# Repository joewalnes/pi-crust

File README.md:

Pi Crust
========

This is a PCB that brings sanity to Raspberry Pi headers.

See [http://picru.st](http://picru.st) for more.

Features
--------

*   Really compact - sits *inside* the surface area of the Raspberry Pi and adds less than 2mm to the height. If you have a case for your Raspberry Pi, this board should fit inside it.
*   Pins are grouped together: GPIO, I2C, SPI, UART and power.
*   Every pin is clearly labelled.
*   Connections: 2 x SPI, 2 x I2C, 1 x UART, 8 x GPIO
*   Uses female headers instead of male headers - you can poke jumpers right in.
*   Lots of GND and 5V pins - you need those guys a lot. These pins are duplicated where it makes sense (e.g. within the UART, I2C and SPI groups).
*   All thru-hole components - you can solder it yourself.
*   Cheapety cheapy cheap.
*   Open source hardware.
*   [More photos here](http://todayimade.co/items/joe-walnes-made-a-tiny-breakout-board-for-raspberry-pi)

See [http://picru.st](http://picru.st) for more.

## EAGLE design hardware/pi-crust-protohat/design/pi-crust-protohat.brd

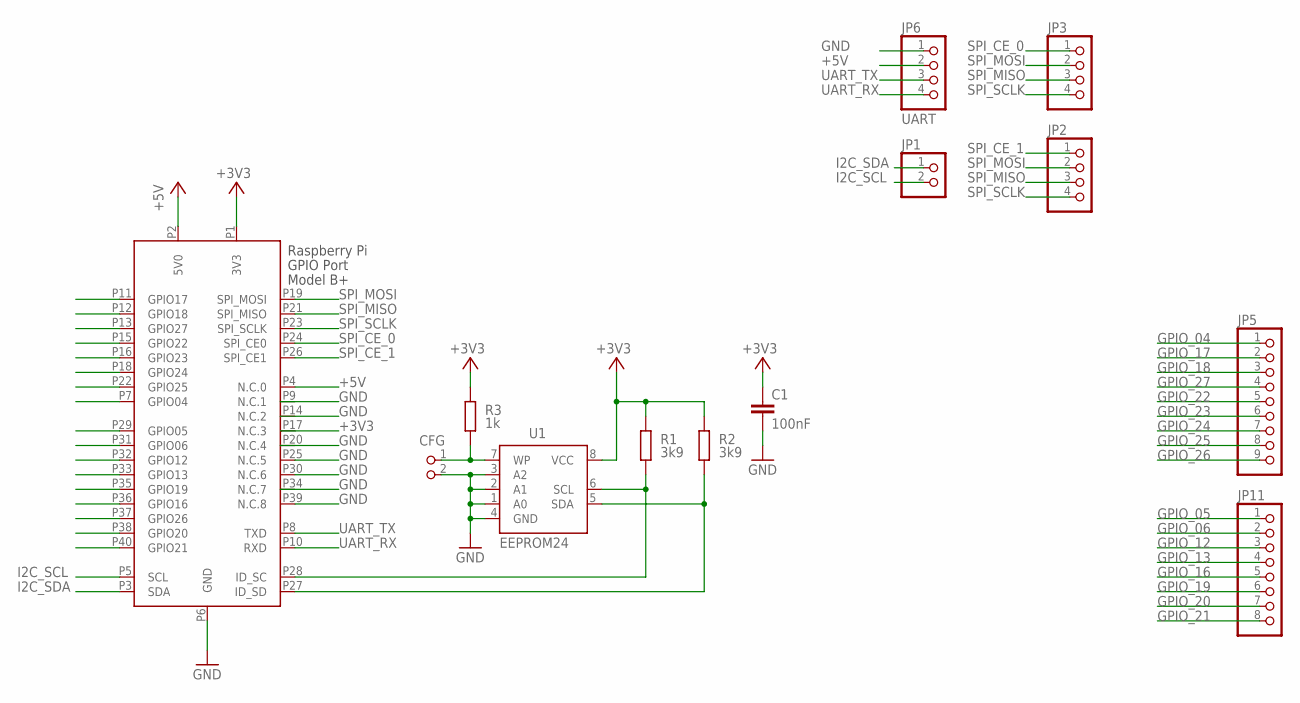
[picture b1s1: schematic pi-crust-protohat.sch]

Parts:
C1: 100nF; C0805K
CFG: PIN2_100; PIN_W_2
JP1: PINHD-1X2; 1X02
JP2, JP3: PINHD-1X4; 1X04
JP5: PINHD-1X9; 1X09
JP6: UART; 1X04
JP11: PINHD-1X8; 1X08
R1, R2: 3k9; M0805; TOLERANCE 5%
R3: 1k; M0805; TOLERANCE 5%
U1: EEPROM24; SOIC8
U$1: RASPI_BOARD_B+_SMD; RASPI_BOARD_B+_SMD_CONNECTOR

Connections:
+3V3: C1.1, R1.2, R2.2, R3.2, U1.8 (VCC), U$1.P1 (3V3)
+5V: JP6.2, U$1.P2 (5V0), U$1.P4 (N.C.0)
GND: C1.2, CFG.2, JP6.1, U1.1 (A0), U1.2 (A1), U1.3 (A2), U1.4 (GND), U$1.P6 (GND), U$1.P25 (N.C.5), U$1.P30 (N.C.6), U$1.P39 (N.C.8)
GPIO_04: JP5.1, U$1.P7 (GPIO04)
GPIO_05: JP11.1, U$1.P29 (GPIO05)
GPIO_06: JP11.2, U$1.P31 (GPIO06)
GPIO_12: JP11.3, U$1.P32 (GPIO12)
GPIO_13: JP11.4, U$1.P33 (GPIO13)
GPIO_16: JP11.5, U$1.P36 (GPIO16)
GPIO_17: JP5.2, U$1.P11 (GPIO17)
GPIO_18: JP5.3, U$1.P12 (GPIO18)
GPIO_19: JP11.6, U$1.P35 (GPIO19)
GPIO_20: JP11.7, U$1.P38 (GPIO20)
GPIO_21: JP11.8, U$1.P40 (GPIO21)
GPIO_22: JP5.5, U$1.P15 (GPIO22)
GPIO_23: JP5.6, U$1.P16 (GPIO23)
GPIO_24: JP5.7, U$1.P18 (GPIO24)
GPIO_25: JP5.8, U$1.P22 (GPIO25)
GPIO_26: JP5.9, U$1.P37 (GPIO26)
GPIO_27: JP5.4, U$1.P13 (GPIO27)
I2C_SCL: JP1.2, U$1.P5 (SCL)
I2C_SDA: JP1.1, U$1.P3 (SDA)
unnamed: CFG.1, R3.1, U1.7 (WP)
unnamed: R1.1, U1.6 (SCL), U$1.P28 (ID_SC)
unnamed: R2.1, U1.5 (SDA), U$1.P27 (ID_SD)
SPI_CE_0: JP3.1, U$1.P24 (SPI_CE0)
SPI_CE_1: JP2.1, U$1.P26 (SPI_CE1)
SPI_MISO: JP2.3, JP3.3, U$1.P21 (SPI_MISO)
SPI_MOSI: JP2.2, JP3.2, U$1.P19 (SPI_MOSI)
SPI_SCLK: JP2.4, JP3.4, U$1.P23 (SPI_SCLK)
UART_RX: JP6.4, U$1.P10 (RXD)
UART_TX: JP6.3, U$1.P8 (TXD)

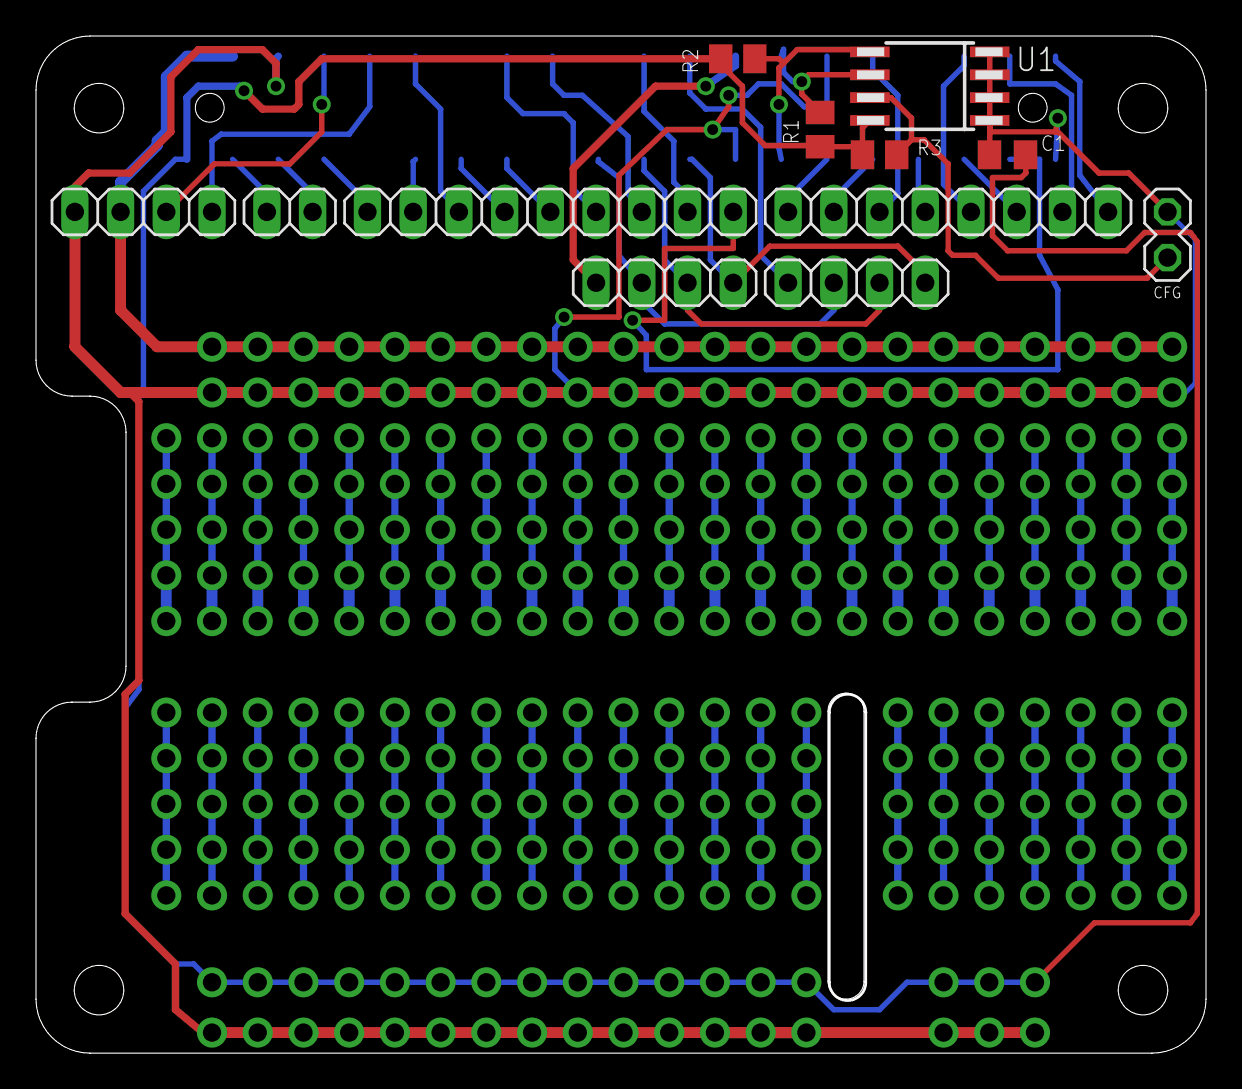
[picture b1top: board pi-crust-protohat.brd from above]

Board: 2 copper layers, 64.8 x 56.4 mm, 13 parts (0 on the bottom side), 32 nets.

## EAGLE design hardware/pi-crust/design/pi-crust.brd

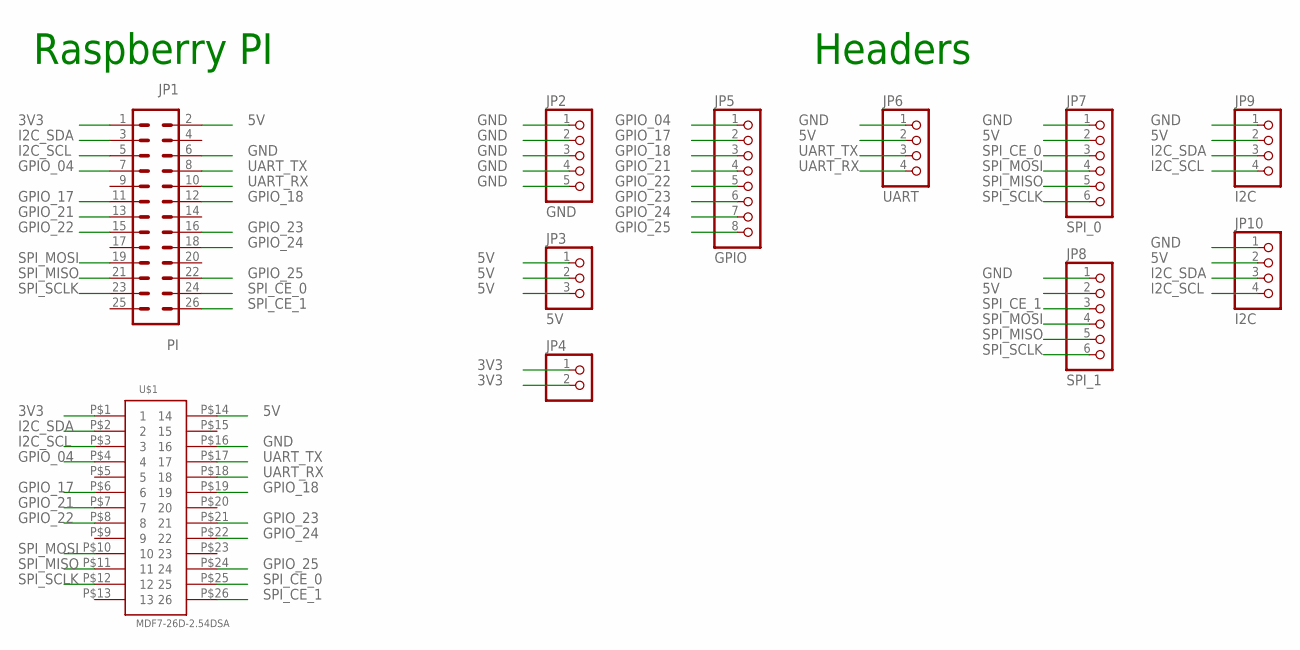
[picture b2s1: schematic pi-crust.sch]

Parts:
JP1: PI; MA13-2
JP2: GND; 1X05
JP3: 5V; 1X03
JP4: PINHD-1X2; 1X02
JP5: GPIO; 1X08
JP6: UART; 1X04
JP7: SPI_0; 1X06
JP8: SPI_1; 1X06
JP9, JP10: I2C; 1X04
U$1: MDF7-26D-2.54DSA

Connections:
3V3: JP1.1, JP4.1, JP4.2, U$1.P$1 (1)
5V: JP1.2, JP3.1, JP3.2, JP3.3, JP6.2, JP7.2, JP8.2, JP9.2, JP10.2, U$1.P$14 (14)
GND: JP1.6, JP2.1, JP2.2, JP2.3, JP2.4, JP2.5, JP6.1, JP7.1, JP8.1, JP9.1, JP10.1, U$1.P$16 (16)
GPIO_04: JP1.7, JP5.1, U$1.P$4 (4)
GPIO_17: JP1.11, JP5.2, U$1.P$6 (6)
GPIO_18: JP1.12, JP5.3, U$1.P$19 (19)
GPIO_21: JP1.13, JP5.4, U$1.P$7 (7)
GPIO_22: JP1.15, JP5.5, U$1.P$8 (8)
GPIO_23: JP1.16, JP5.6, U$1.P$21 (21)
GPIO_24: JP1.18, JP5.7, U$1.P$22 (22)
GPIO_25: JP1.22, JP5.8, U$1.P$24 (24)
I2C_SCL: JP1.5, JP9.4, JP10.4, U$1.P$3 (3)
I2C_SDA: JP1.3, JP9.3, JP10.3, U$1.P$2 (2)
SPI_CE_0: JP1.24, JP7.3, U$1.P$25 (25)
SPI_CE_1: JP1.26, JP8.3, U$1.P$26 (26)
SPI_MISO: JP1.21, JP7.5, JP8.5, U$1.P$11 (11)
SPI_MOSI: JP1.19, JP7.4, JP8.4, U$1.P$10 (10)
SPI_SCLK: JP1.23, JP7.6, JP8.6, U$1.P$12 (12)
UART_RX: JP1.10, JP6.4, U$1.P$18 (18)
UART_TX: JP1.8, JP6.3, U$1.P$17 (17)

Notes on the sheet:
Raspberry PI
Headers

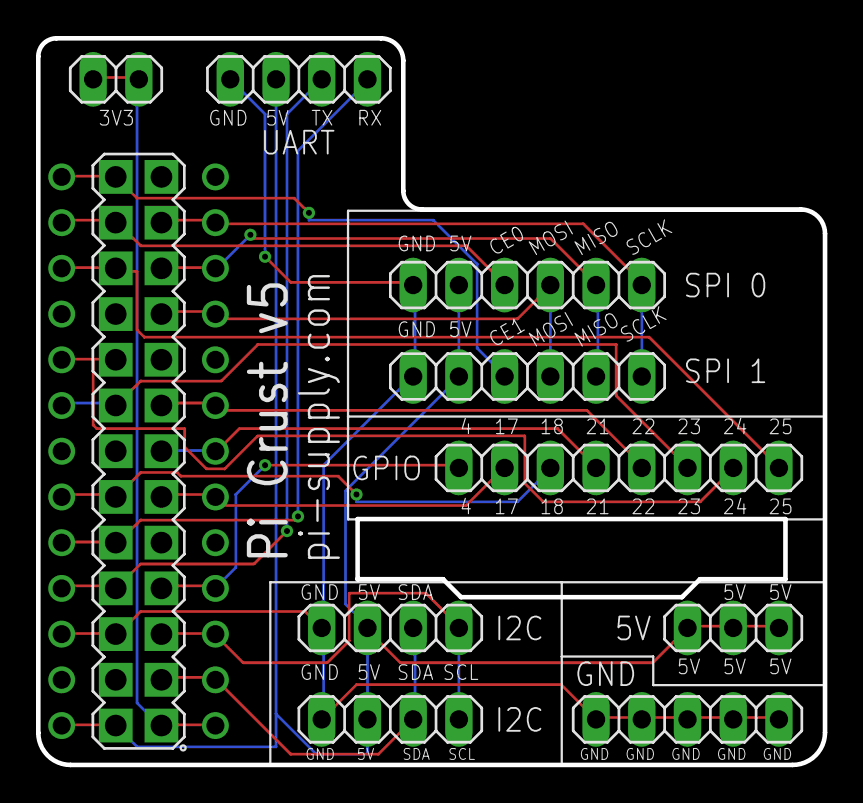
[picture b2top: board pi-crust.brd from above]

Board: 2 copper layers, 43.7 x 40.4 mm, 11 parts (1 on the bottom side), 20 nets.

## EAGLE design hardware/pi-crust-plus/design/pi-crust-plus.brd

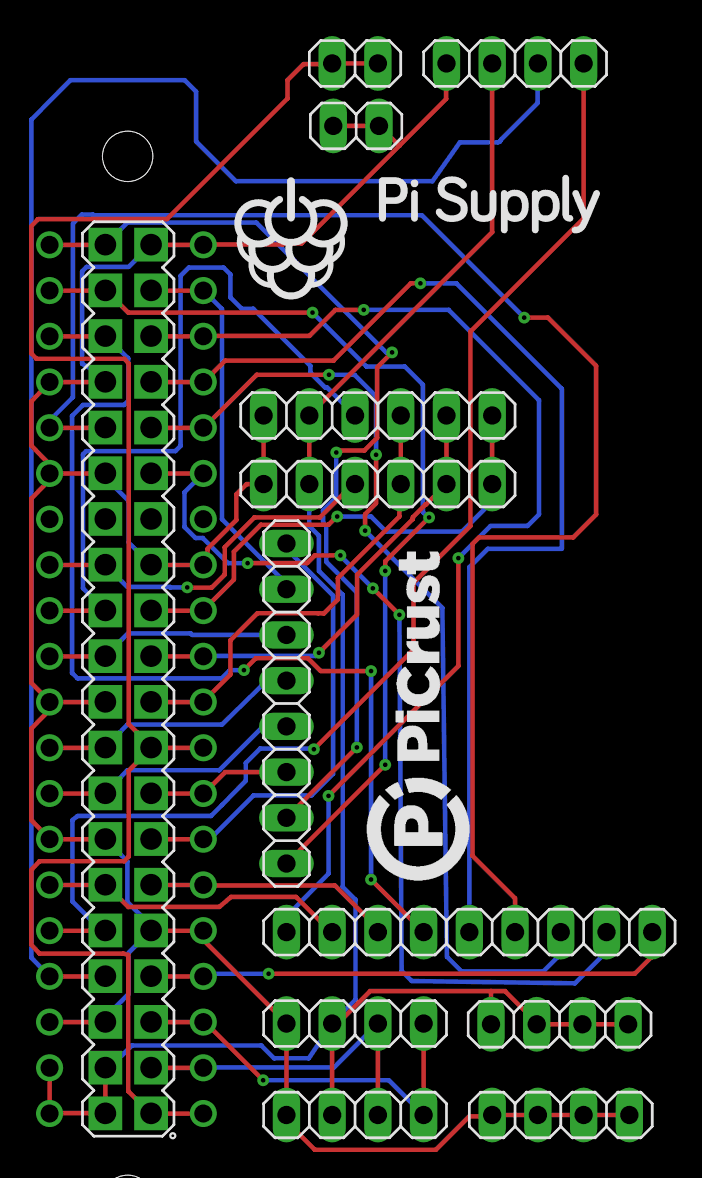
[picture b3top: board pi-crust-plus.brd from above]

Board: 2 copper layers, 13 parts (1 on the bottom side), 29 nets.

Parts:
JP1: GND; 1X04
JP2: GND; 1X02
JP3: 5V; 1X04
JP4: 3V3; 1X02
JP5: 1X09
JP6: UART; 1X04
JP7: SPI 0; 1X06
JP8: SPI 1; 1X06
JP9, JP10: I2C; 1X04
JP11: 1X08
SV1: MA20-2
U$1: MDF7-40D-2.54DSA

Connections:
3V3: JP4.1, JP4.2, SV1.1, SV1.17, U$1.P$1, U$1.P$9
5V: JP3.1, JP3.2, JP3.3, JP3.4, JP6.2, JP7.2, JP8.2, JP9.2, JP10.2, SV1.2, SV1.4, U$1.P$21, U$1.P$22
GND: JP1.1, JP1.2, JP1.3, JP1.4, JP2.1, JP2.2, JP6.1, JP7.1, JP8.1, JP9.1, JP10.1, SV1.6, SV1.9, SV1.14, SV1.20, SV1.25, SV1.30, SV1.34, SV1.39, U$1.P$5, U$1.P$13, U$1.P$20, U$1.P$23, U$1.P$27, U$1.P$30, U$1.P$35, U$1.P$37
GPIO_04: JP5.1, SV1.7, U$1.P$4
GPIO_05: JP5.2, SV1.29, U$1.P$15
GPIO_06: JP5.3, SV1.31, U$1.P$16
GPIO_12: JP5.4, SV1.32, U$1.P$36
GPIO_13: JP5.5, SV1.33, U$1.P$17
GPIO_16: JP5.6, SV1.36, U$1.P$38
GPIO_17: JP5.7, SV1.11, U$1.P$6
GPIO_18: JP5.8, SV1.12, U$1.P$26
GPIO_19: JP5.9, SV1.35, U$1.P$18
GPIO_20: JP11.1, SV1.38, U$1.P$39
GPIO_21: JP11.2, SV1.40, U$1.P$40
GPIO_22: JP11.3, SV1.15, U$1.P$8
GPIO_23: JP11.4, SV1.16, U$1.P$28
GPIO_24: JP11.5, SV1.18, U$1.P$29
GPIO_25: JP11.6, SV1.22, U$1.P$31
GPIO_26: JP11.7, SV1.37, U$1.P$19
GPIO_27: JP11.8, SV1.13, U$1.P$7
I2C_SCL: JP9.4, JP10.4, SV1.5, U$1.P$3
I2C_SDA: JP9.3, JP10.3, SV1.3, U$1.P$2
SPI_CE_0: JP7.3, SV1.24, U$1.P$32
SPI_CE_1: JP8.3, SV1.26, U$1.P$33
SPI_MISO: JP7.5, JP8.5, SV1.21, U$1.P$11
SPI_MOSI: JP7.4, JP8.4, SV1.19, U$1.P$10
SPI_SCLK: JP7.6, JP8.6, SV1.23, U$1.P$12
UART_RX: JP6.4, SV1.10, U$1.P$25
UART_TX: JP6.3, SV1.8, U$1.P$24

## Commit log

2012-07-04 First cut of schematic
2012-07-04 Makefile to generate and view gerbers
2012-07-04 Schematic jumpers all have values. Eagle electrical rule check now passes
2012-07-04 Improved schematic layout
2012-07-04 Rearrange labels and make a bit more space for routing paths
2012-07-05 Removed airflow hole (made board unroutable), mitred edges and routed wires.
2012-07-05 Added labels and section dividers to silkscreen layer
2012-07-05 README
2012-07-05 Added PCB image screenshot
2012-07-05 Ignore VIM swap files
2012-07-05 Added image to README
2012-07-05 Fix image link
2012-07-05 Added parts list and assembly instructions.
2012-07-05 Add link to photo of Pi measurements
2012-07-06 Created custom part for Pi connector, with drills that fit the pin insert components.
2012-07-10 Manually routed by Mercedes
2012-07-10 Moved all labels from tValues to tNames layer, so they appear on the silkscreen.
2012-08-28 Added marks on bottom to show where to attach support feet.
2012-08-28 Moved one of the vias so its not so close to the headers.
2012-08-28 Elongate board slot, as it was a wee bit too short.
2012-08-30 Increased diameter of solder pads around 26 pin connectors to make it easier to solder inserts.
2012-08-30 PiCrust V2:
    * Made 26 pin connector pads square, so it's easy to dab solder over
    the edges of the pin inserts.
    * Vias are smaller and tented.
    * Minor re-routing around some tight areas.
    * Added text to silk screen.
2012-09-18 v3 board. With Hirose 26 pin connector.
2012-10-09 V4: Replaced single 3V3 header with a double. Actually makes it cheaper to make and a 2nd connector is always handy. Shuffled the UART along a little.
2012-10-09 updated image
2012-10-09 Updated instructions and BOM
2012-10-09 Added photo, fixed some links
2012-10-09 Link to more photos
2012-10-10 right click, save as
2012-10-11 Clarified first photo
2012-10-24 Create gh-pages branch via GitHub
2012-10-24 Migrated content from README to website.
2012-10-24 GitHub CNAME picrust.joewalnes.com
2012-10-24 Added logo
2012-10-24 gitignore
2012-10-24 New domain: picru.st (yeah, its obnoxious)
2012-10-24 Added guag.es tracker.
2012-10-24 Add google analytics
2012-10-24 Photos, navigation, and some content tweaks
2012-10-24 clean footer
2012-10-24 CSS tweaks
2012-10-24 Link to new website
2012-10-24 Added Uservoice feedback widget.
2012-10-24 Reduced filesize of massive photos.
2012-10-25 GoSquared analytics
2012-10-25 Added Quick2Wire plug
2012-10-25 s/Designed by/By/
2012-10-25 Update Salman's link
2012-10-25 Added oshpark store link and new price.
2012-10-25 Pretty update box
2012-10-25 Out with UserVoice, in with Google Groups
2012-10-25 Added twitter plug and cleaned up the header so it has less distractions.
2012-10-25 Cleaned up nav
2012-10-25 Fork me on github banner
2012-10-26 Changed shape of hole to accomodate new DSI connector cover on RPi rev 2.
2012-10-28 Fixed silkscreen text
2012-10-31 Automate gerber export. Just run make.
2012-11-02 Fix indentation
2012-11-02 Indentation
2012-11-04 Special edition PS1 silkscreen
2012-11-04 Fixed up silkscreen
2012-12-03 Fixed oshpark link.
2013-01-03 Dont include solder paste layers in gerbers - not used.
2013-03-12 Bunch of updates
2013-03-12 copy in 1st person
2013-03-12 more rejiggling
2013-03-13 social buttons
2013-03-13 s/newsletter/news updates/
2013-03-13 Added examples and resources
2013-03-13 font sizes
2013-05-28 pi-supply.com version
2013-12-17 Add a Bitdeli badge to README
2017-03-26 Initialise hardware folder
    Initialise hardware folder
2017-03-27 reorganise, add gerbers, add picrust plus and protohat
    reorganise, add gerbers, add picrust plus and protohat
2017-03-27 update picrust original design
    update picrust original design
2017-04-12 update hardware designs for plus and protohat
    update hardware designs for plus and protohat
